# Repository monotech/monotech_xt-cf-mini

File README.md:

Monotech XT-CF-Mini Rev1.1 ReadMe
----------------------------

8-bit ISA CompactFlash interface + Boot ROM (two separate functions that can be used individually).

Documentation for the switches can be found on the rear silkscreen. More ROM I/O addresses are possible than the information on the silkscreen. See below.

Credit:
-------
Design uses schematic from Sergey Kiselev, with a few small changes to switches, and PCB from scratch.\
www.malinov.com/Home/sergeys-projects/xt-cf-lite

XT-IDE Universal BIOS\
www.xtideuniversalbios.org  
www.xtideuniversalbios.org/binaries  
Use the latest working binary that includes XTIDECFG.COM (config utility), ide_xt.bin (8086/8088), ide_xtp.bin (80186/V20/V30 and up).

Further documentation:
----------------------

SW1 - ON: ROM Enabled; OFF: ROM Disabled\
SW2 - ON: EEPROM Write Enabled; OFF: EEPROM Write Disabled

---

SW3 - ROM I/O Port:  
123 ROM  
111 C0000  
111 C2000*  
110 C4000  
110 C6000*  
101 C8000  
101 CA000  
100 CC000  
100 CE000*  
011 D0000 < Default  
011 D2000*  
010 D4000  
010 D6000*  
001 D8000  
001 DA000*  
000 DC000  
000 DE000*  
111 E0000**  
111 E2000***  
110 E4000**  
110 E6000***  
101 E8000**  
101 EA000***  
100 EC000**  
100 EE000***  
011 F0000**  
011 F2000***  
010 F4000**  

Settings marked with asterisks require solder-jumpers to be opened:

Settings marked with * require JP1 to be opened.\
Settings marked with ** require JP2 to be opened.\
Settings marked with *** require both JP1 and JP2 to be opened.\
Settings marked with no *, are set with the three DIP switches, and require JP1 and JP2 to be closed.\

Make sure that selected I/O and EEPROM addresses do not conflict with other devices.\
Addresses 0xC0000 - 0xC6000 will conflict with EGA/VGA BIOS extension.\
Addresses 0xC8000 - 0xCA000 might conflict with XT Hard Disk BIOS extension.\
Addresses 0xE0000 and up might conflict with system BIOS on newer motherboards.\
It is recommended to disable EEPROM write once XT IDE BIOS extension is programmed and configured.

---

SW4 - IDE I/O Port:  
123 IDE  
111 300 < Default  
011 320  
101 340  
001 360  
110 380  
010 3A0  
100 3C0  
000 3E0  

The A8 line is provided as a solder-jumper JP3, and should change the first digit of the IDE I/O Port from 3 to 2 (so 300 becomes 200, 3C0 becomes 2C0, etc). This is untested at present.\

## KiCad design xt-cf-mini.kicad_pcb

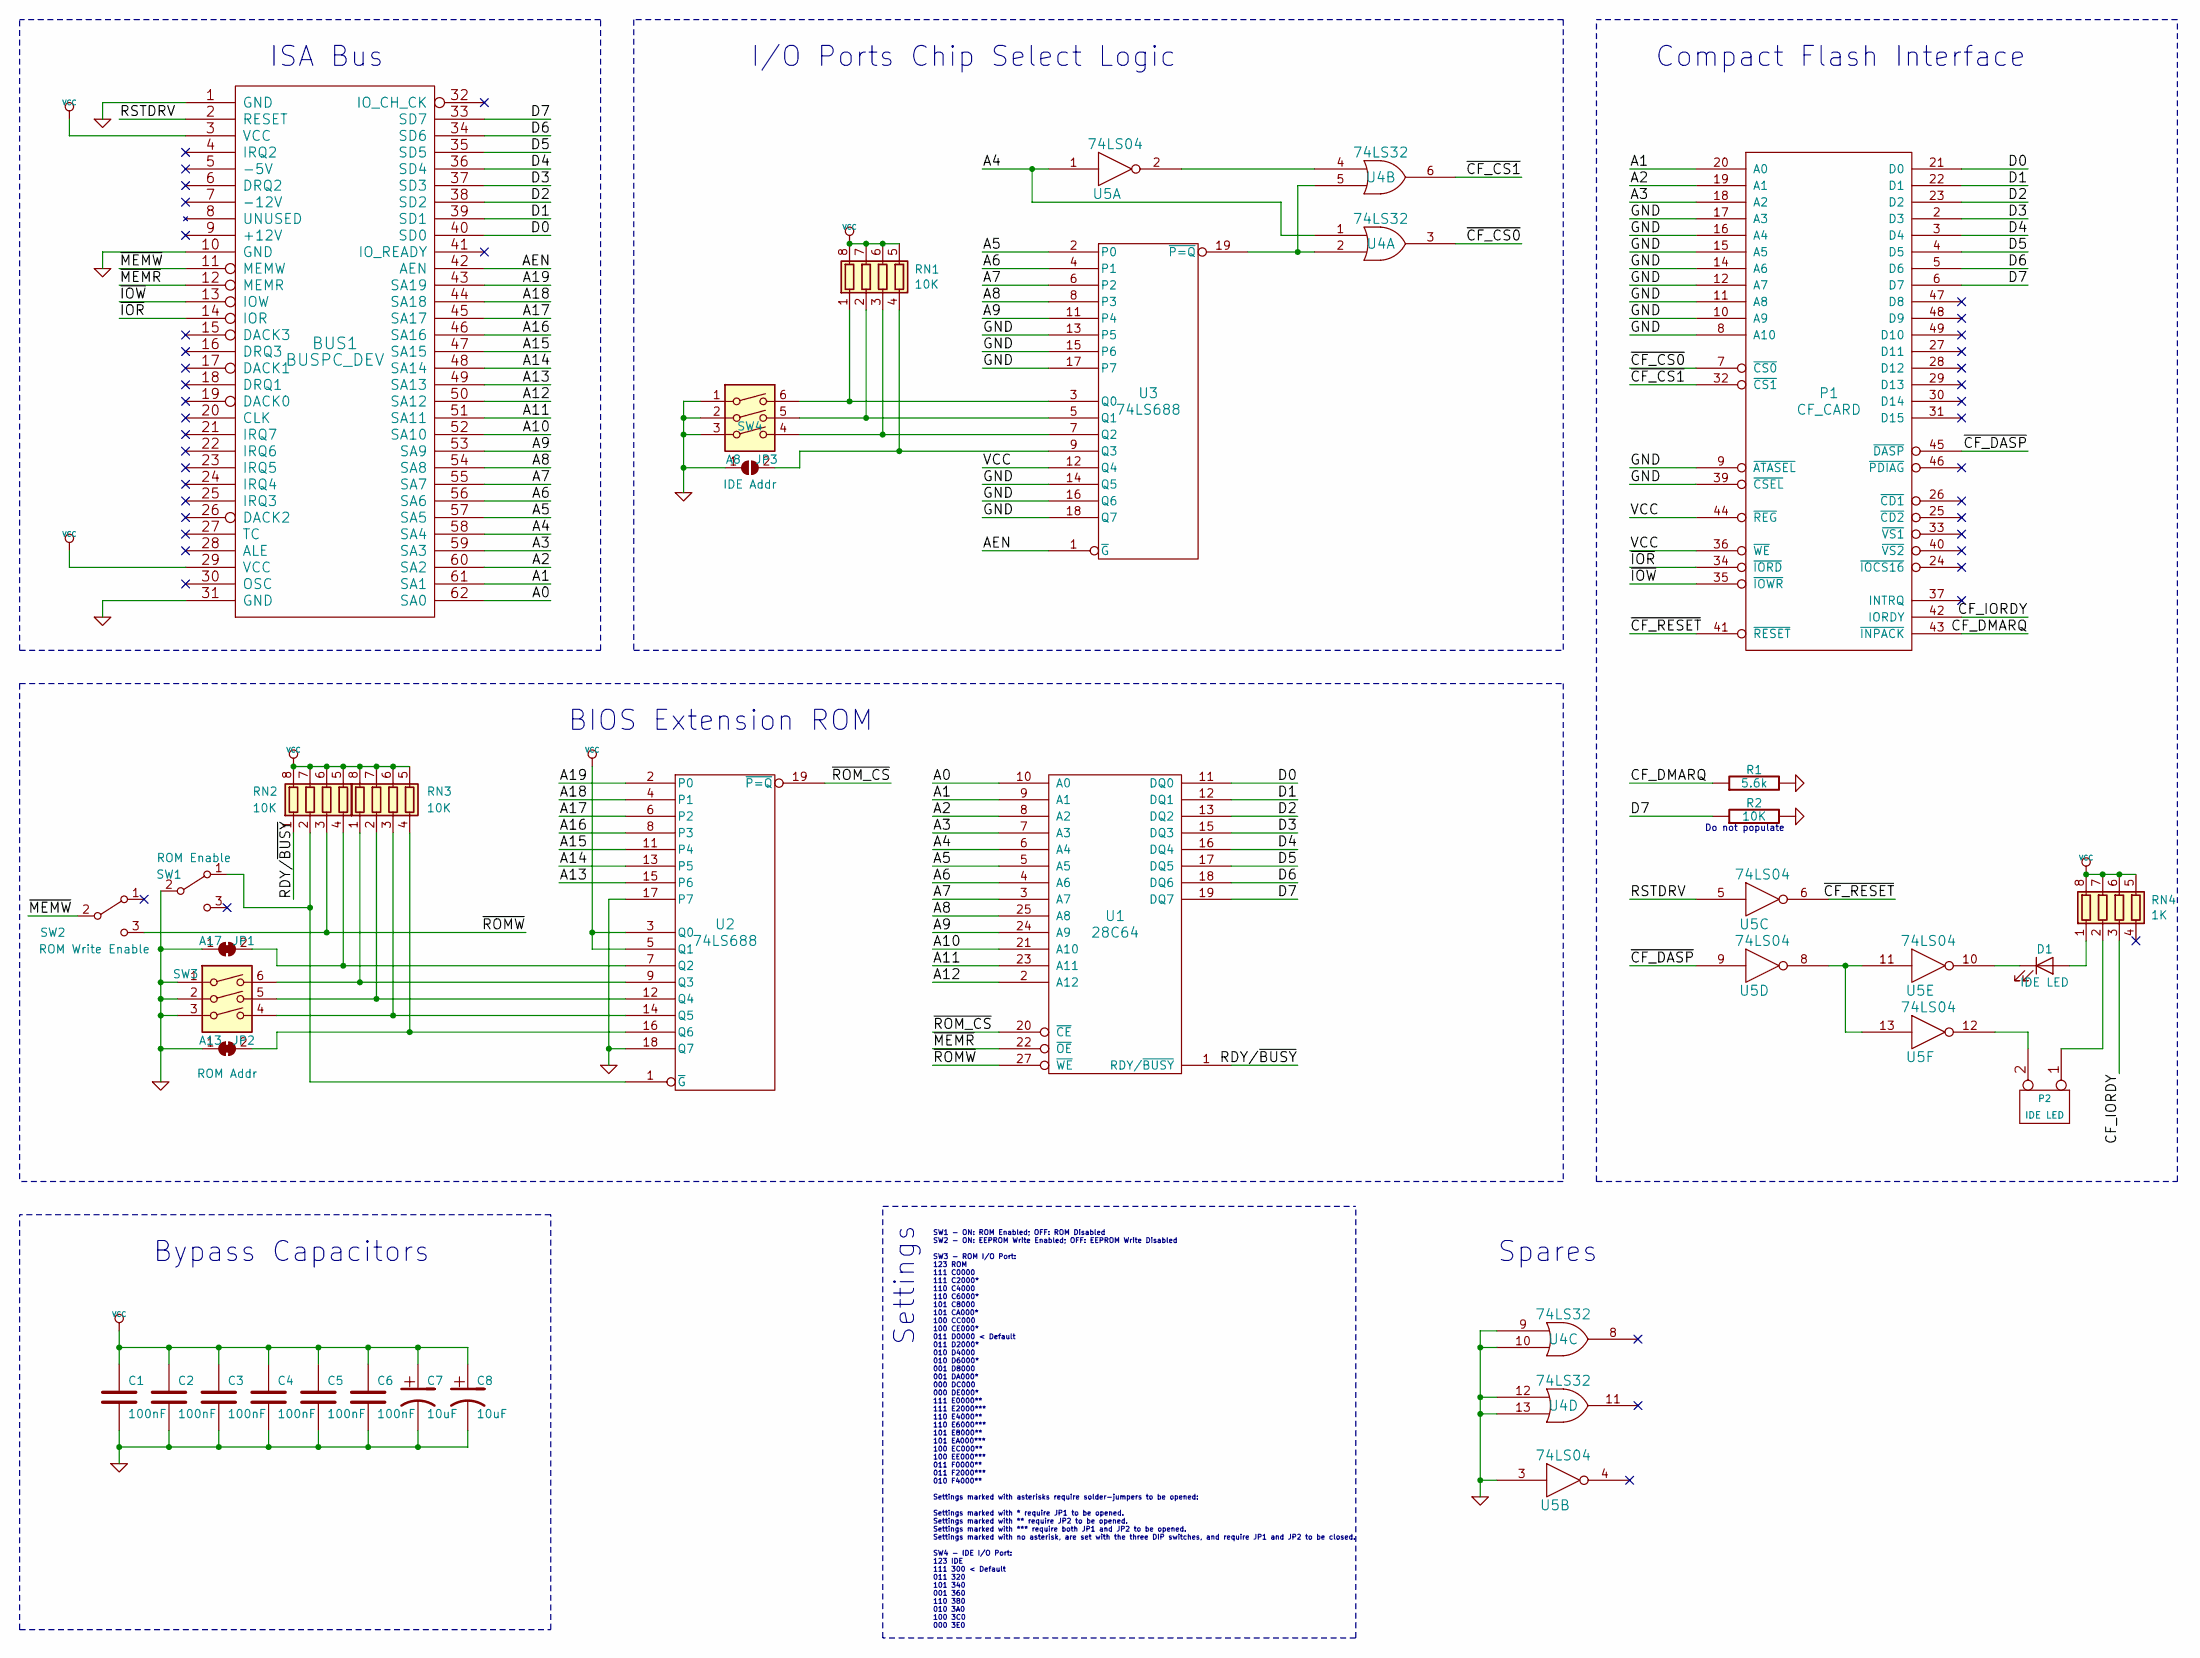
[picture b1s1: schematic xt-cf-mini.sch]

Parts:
BUS1: BUSPC_DEV; ISA-8BIT-XT-CF
C1, C2, C3, C4, C5, C6: 100nF; C_0805_2012Metric_Pad1.15x1.40mm_HandSolder
C7, C8: 10uF; C_0805_2012Metric_Pad1.15x1.40mm_HandSolder
D1: IDE LED; LED_D3.0mm
JP1: A17; SolderJumper-2_P1.3mm_Open_Pad1.0x1.5mm
JP2: A13; SolderJumper-2_P1.3mm_Open_Pad1.0x1.5mm
JP3: A8; SolderJumper-2_P1.3mm_Open_Pad1.0x1.5mm
P1: CF_CARD; CF_Slot_3M_N7E50-7516TS0884
P2: IDE LED; PinHeader_1x02_P2.54mm_Horizontal
R1: 5.6k; C_0805_2012Metric_Pad1.15x1.40mm_HandSolder
R2: 10K; C_0805_2012Metric_Pad1.15x1.40mm_HandSolder
RN1, RN2, RN3: 10K; R_Array_Convex_4x1206
RN4: 1K; R_Array_Convex_4x1206
SW1: ROM Enable; CKCOMP-OS102011MA1QN1
SW2: ROM Write Enable; CKCOMP-OS102011MA1QN1
SW3: ROM Addr; SW_DIP_SPSTx03_Slide_9.78x9.8mm_W7.62mm_P2.54mm
SW4: IDE Addr; SW_DIP_SPSTx03_Slide_9.78x9.8mm_W7.62mm_P2.54mm
U1: 28C64; DIP-28_W15.24mm_Socket
U2, U3: 74LS688; SOIC-20W_7.5x12.8mm_P1.27mm
U4: 74LS32; SOIC-14_3.9x8.7mm_P1.27mm
U5: 74LS04; SOIC-14_3.9x8.7mm_P1.27mm

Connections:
/A0: BUS1.62 (SA0), U1.10 (A0)
/A1: BUS1.61 (SA1), P1.20 (A0), U1.9 (A1)
/A2: BUS1.60 (SA2), P1.19 (A1), U1.8 (A2)
/A3: BUS1.59 (SA3), P1.18 (A2), U1.7 (A3)
/A4: BUS1.58 (SA4), U1.6 (A4), U4.1, U5.1
/A5: BUS1.57 (SA5), U1.5 (A5), U3.2 (P0)
/A6: BUS1.56 (SA6), U1.4 (A6), U3.4 (P1)
/A7: BUS1.55 (SA7), U1.3 (A7), U3.6 (P2)
/A8: BUS1.54 (SA8), U1.25 (A8), U3.8 (P3)
/A9: BUS1.53 (SA9), U1.24 (A9), U3.11 (P4)
/A10: BUS1.52 (SA10), U1.21 (A10)
/A11: BUS1.51 (SA11), U1.23 (A11)
/A12: BUS1.50 (SA12), U1.2 (A12)
/A13: BUS1.49 (SA13), U2.15 (P6)
/A14: BUS1.48 (SA14), U2.13 (P5)
/A15: BUS1.47 (SA15), U2.11 (P4)
/A16: BUS1.46 (SA16), U2.8 (P3)
/A17: BUS1.45 (SA17), U2.6 (P2)
/A18: BUS1.44 (SA18), U2.4 (P1)
/A19: BUS1.43 (SA19), U2.2 (P0)
/AEN: BUS1.42 (AEN), U3.1 (~G)
/CF_DMARQ: P1.43 (~INPACK), R1.1
/CF_IORDY: P1.42 (IORDY), RN4.3 (R3.1)
/D0: BUS1.40 (SD0), P1.21 (D0), U1.11 (DQ0)
/D1: BUS1.39 (SD1), P1.22 (D1), U1.12 (DQ1)
/D2: BUS1.38 (SD2), P1.23 (D2), U1.13 (DQ2)
/D3: BUS1.37 (SD3), P1.2 (D3), U1.15 (DQ3)
/D4: BUS1.36 (SD4), P1.3 (D4), U1.16 (DQ4)
/D5: BUS1.35 (SD5), P1.4 (D5), U1.17 (DQ5)
/D6: BUS1.34 (SD6), P1.5 (D6), U1.18 (DQ6)
/D7: BUS1.33 (SD7), P1.6 (D7), R2.1, U1.19 (DQ7)
/RDY/~BUSY: RN2.1 (R1.1), U1.1 (RDY/~BUSY)
/RSTDRV: BUS1.2 (RESET), U5.5
/~CF_CS0: P1.7 (~CS0), U4.3
/~CF_CS1: P1.32 (~CS1), U4.6
/~CF_DASP: P1.45 (~DASP), U5.9
/~CF_RESET: P1.41 (~RESET), U5.6
/~IOR: BUS1.14 (IOR), P1.34 (~IORD)
/~IOW: BUS1.13 (IOW), P1.35 (~IOWR)
/~MEMR: BUS1.12 (MEMR), U1.22 (~OE)
/~MEMW: BUS1.11 (MEMW), SW2.2 (B)
/~ROMW: RN2.3 (R3.1), SW2.3 (C), U1.27 (~WE)
/~ROM_CS: U1.20 (~CE), U2.19 (~P=Q)
GND: BUS1.1 (GND), BUS1.10 (GND), BUS1.31 (GND), C1.2, C2.2, C3.2, C4.2, C5.2, C6.2, C7.2, C8.2, JP1.1 (A), JP2.1 (A), JP3.1 (A), P1.1 (GND), P1.8 (A10), P1.9 (~ATASEL), P1.10 (A9), P1.11 (A8), P1.12 (A7), P1.14 (A6), P1.15 (A5), P1.16 (A4), P1.17 (A3), P1.39 (~CSEL), P1.50 (GND), R1.2, R2.2, SW1.2 (B), SW3.1, SW3.2, SW3.3, SW4.1, SW4.2, SW4.3, U1.14 (GND), U2.10 (GND), U2.17 (P7), U2.18 (Q7), U3.10 (GND), U3.13 (P5), U3.14 (Q5), U3.15 (P6), U3.16 (Q6), U3.17 (P7), U3.18 (Q7), U4.7 (GND), U4.9, U4.10, U4.12, U4.13, U5.3, U5.7 (GND)
unnamed: D1.1 (K), U5.10
unnamed: D1.2 (A), RN4.1 (R1.1)
unnamed: JP1.2 (B), RN2.4 (R4.1), U2.7 (Q2)
unnamed: JP2.2 (B), RN3.4 (R4.1), U2.16 (Q6)
unnamed: JP3.2 (B), RN1.4 (R4.1), U3.9 (Q3)
unnamed: P2.1, RN4.2 (R2.1)
unnamed: P2.2 (PM), U5.12
unnamed: RN1.1 (R1.1), SW4.6, U3.3 (Q0)
unnamed: RN1.2 (R2.1), SW4.5, U3.5 (Q1)
unnamed: RN1.3 (R3.1), SW4.4, U3.7 (Q2)
unnamed: RN2.2 (R2.1), SW1.1 (A), U2.1 (~G)
unnamed: RN3.1 (R1.1), SW3.6, U2.9 (Q3)
unnamed: RN3.2 (R2.1), SW3.5, U2.12 (Q4)
unnamed: RN3.3 (R3.1), SW3.4, U2.14 (Q5)
unnamed: U3.19 (~P=Q), U4.2, U4.5
unnamed: U4.4, U5.2
unnamed: U5.8, U5.11, U5.13
VCC: BUS1.3 (VCC), BUS1.29 (VCC), C1.1, C2.1, C3.1, C4.1, C5.1, C6.1, C7.1, C8.1, P1.13 (VCC), P1.36 (~WE), P1.38 (VCC), P1.44 (~REG), RN1.5 (R4.2), RN1.6 (R3.2), RN1.7 (R2.2), RN1.8 (R1.2), RN2.5 (R4.2), RN2.6 (R3.2), RN2.7 (R2.2), RN2.8 (R1.2), RN3.5 (R4.2), RN3.6 (R3.2), RN3.7 (R2.2), RN3.8 (R1.2), RN4.5 (R4.2), RN4.6 (R3.2), RN4.7 (R2.2), RN4.8 (R1.2), U1.28 (VCC), U2.3 (Q0), U2.5 (Q1), U2.20 (VCC), U3.12 (Q4), U3.20 (VCC), U4.14 (VCC), U5.14 (VCC)

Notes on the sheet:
Spares
ISA Bus
BIOS Extension ROM
Bypass Capacitors
I/O Ports Chip Select Logic
Compact Flash Interface
SW1 - ON: ROM Enabled; OFF: ROM Disabled SW2 - ON: EEPROM Write Enabled; OFF: EEPROM Write Disabled SW3 - ROM I/O Port: 123 ROM 111 C0000 111 C2000* 110 C4000 110 C6000* 101 C8000 101 CA000* 100 CC000 100 CE000* 011 D0000 < Default 011 D2000* 010 D4000 010 D6000* 001 D8000 001 DA000* 000 DC000 000 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
Settings
Do not populate

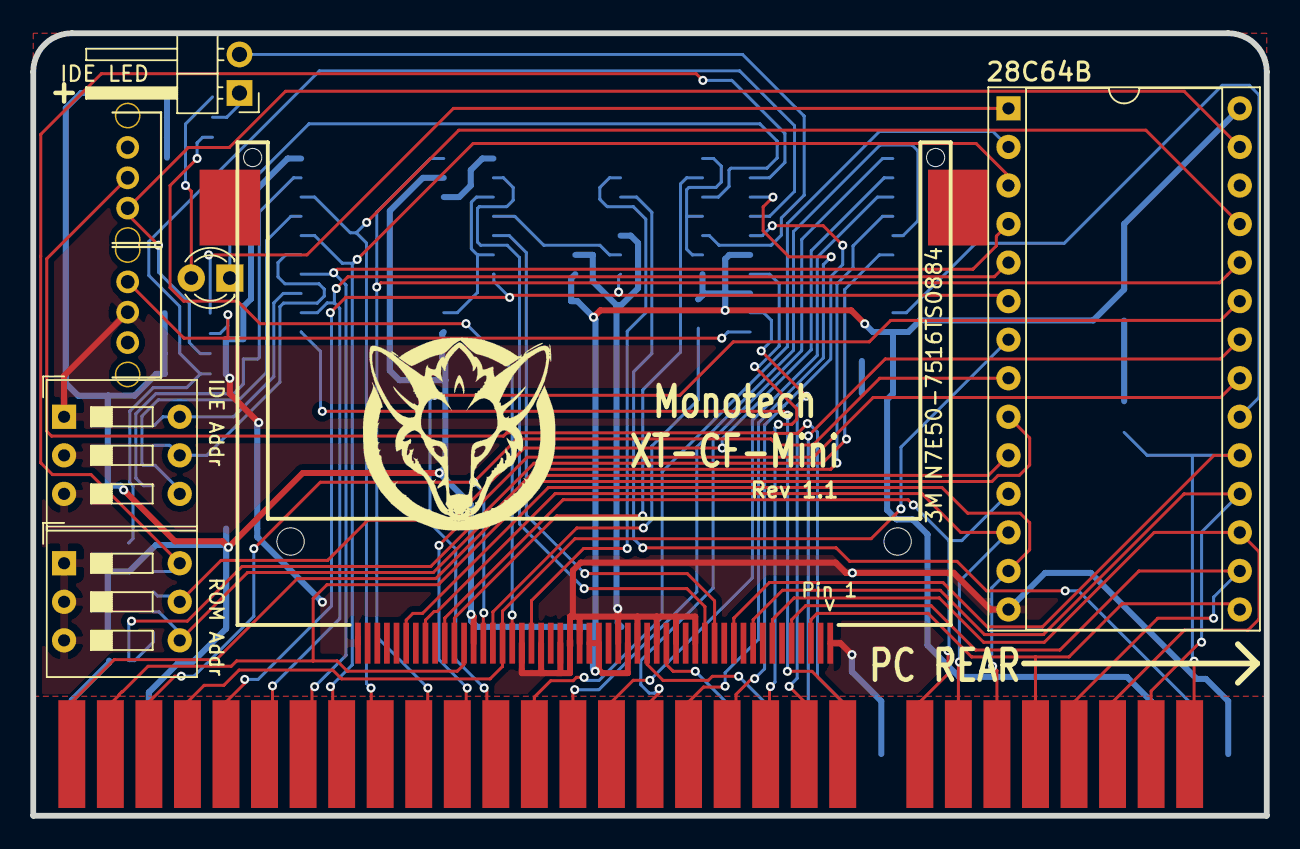
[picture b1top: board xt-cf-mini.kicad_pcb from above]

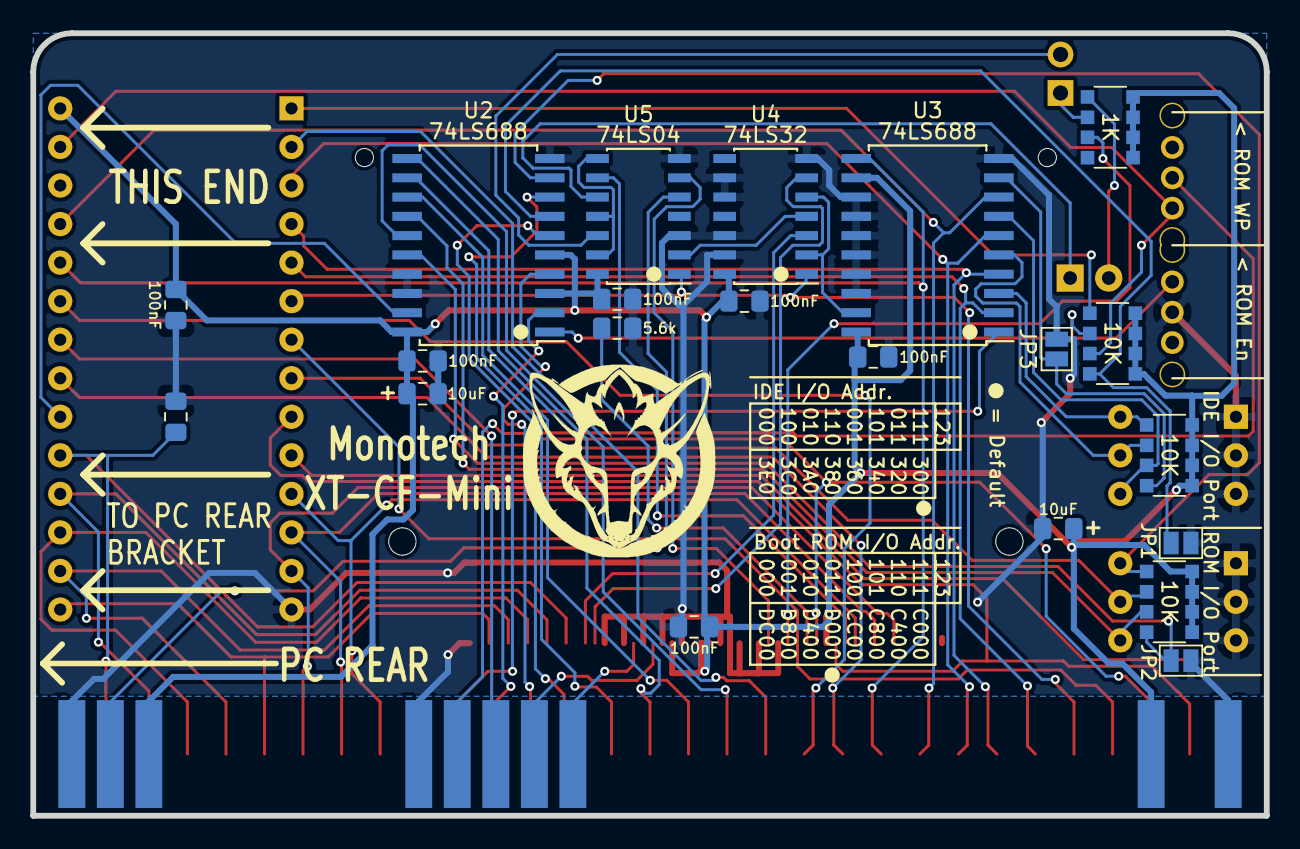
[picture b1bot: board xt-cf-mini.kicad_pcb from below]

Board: 2 copper layers, 81.3 x 51.6 mm, 30 parts (21 on the bottom side), 62 nets.
